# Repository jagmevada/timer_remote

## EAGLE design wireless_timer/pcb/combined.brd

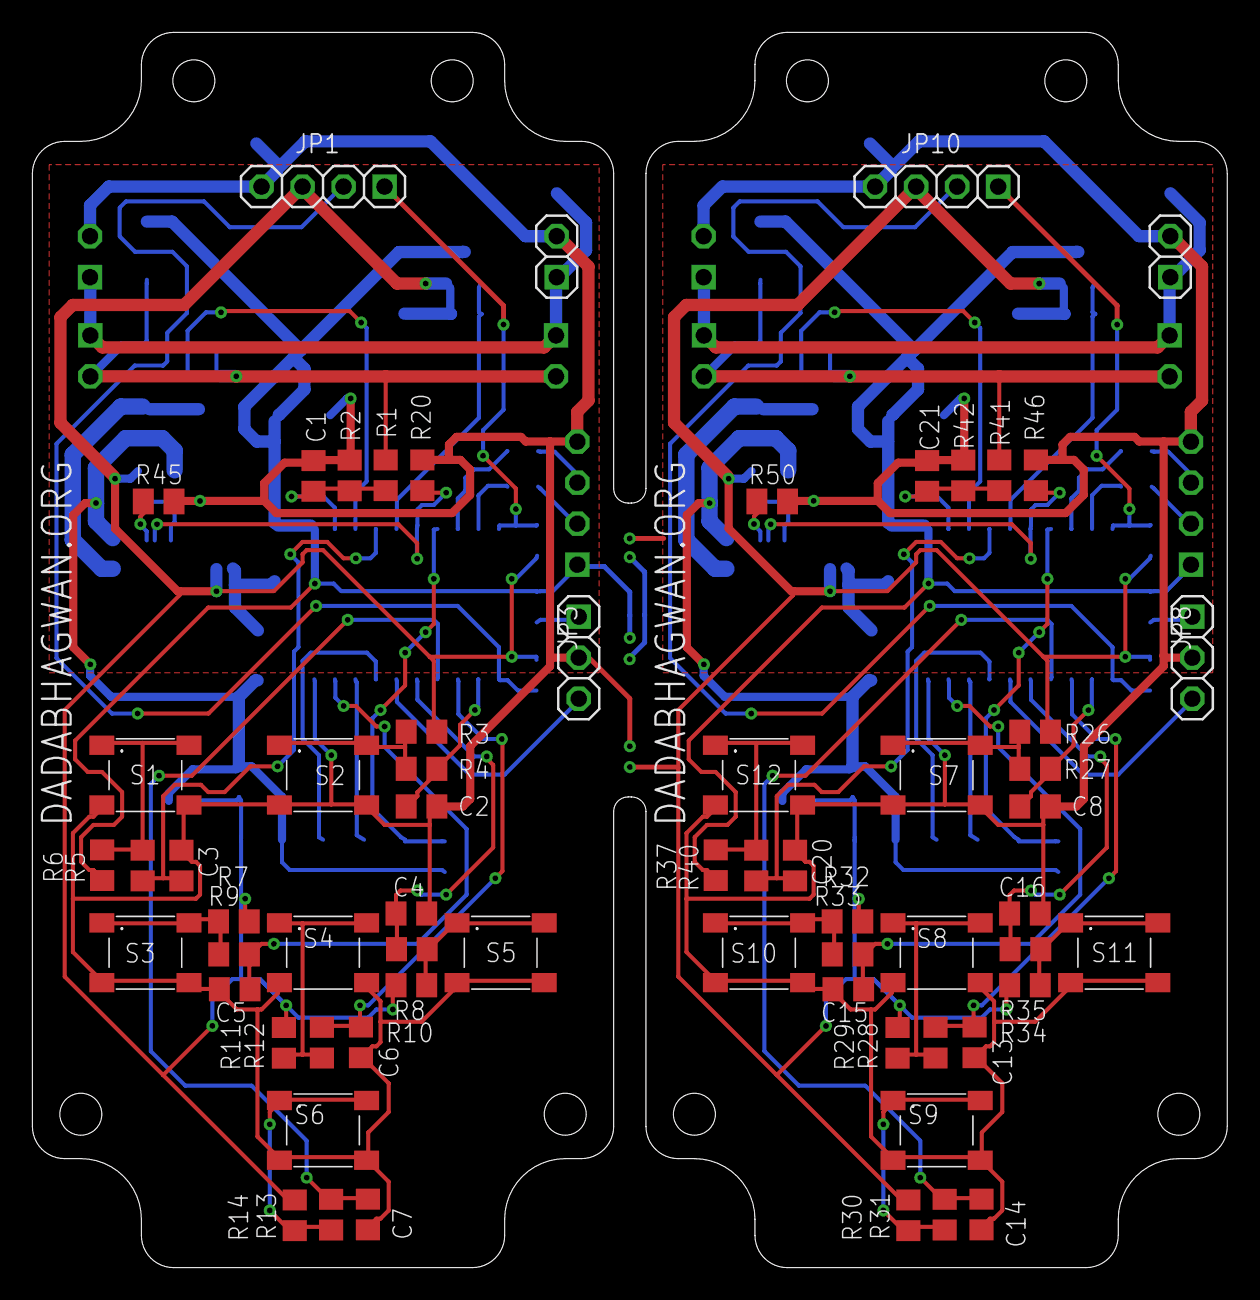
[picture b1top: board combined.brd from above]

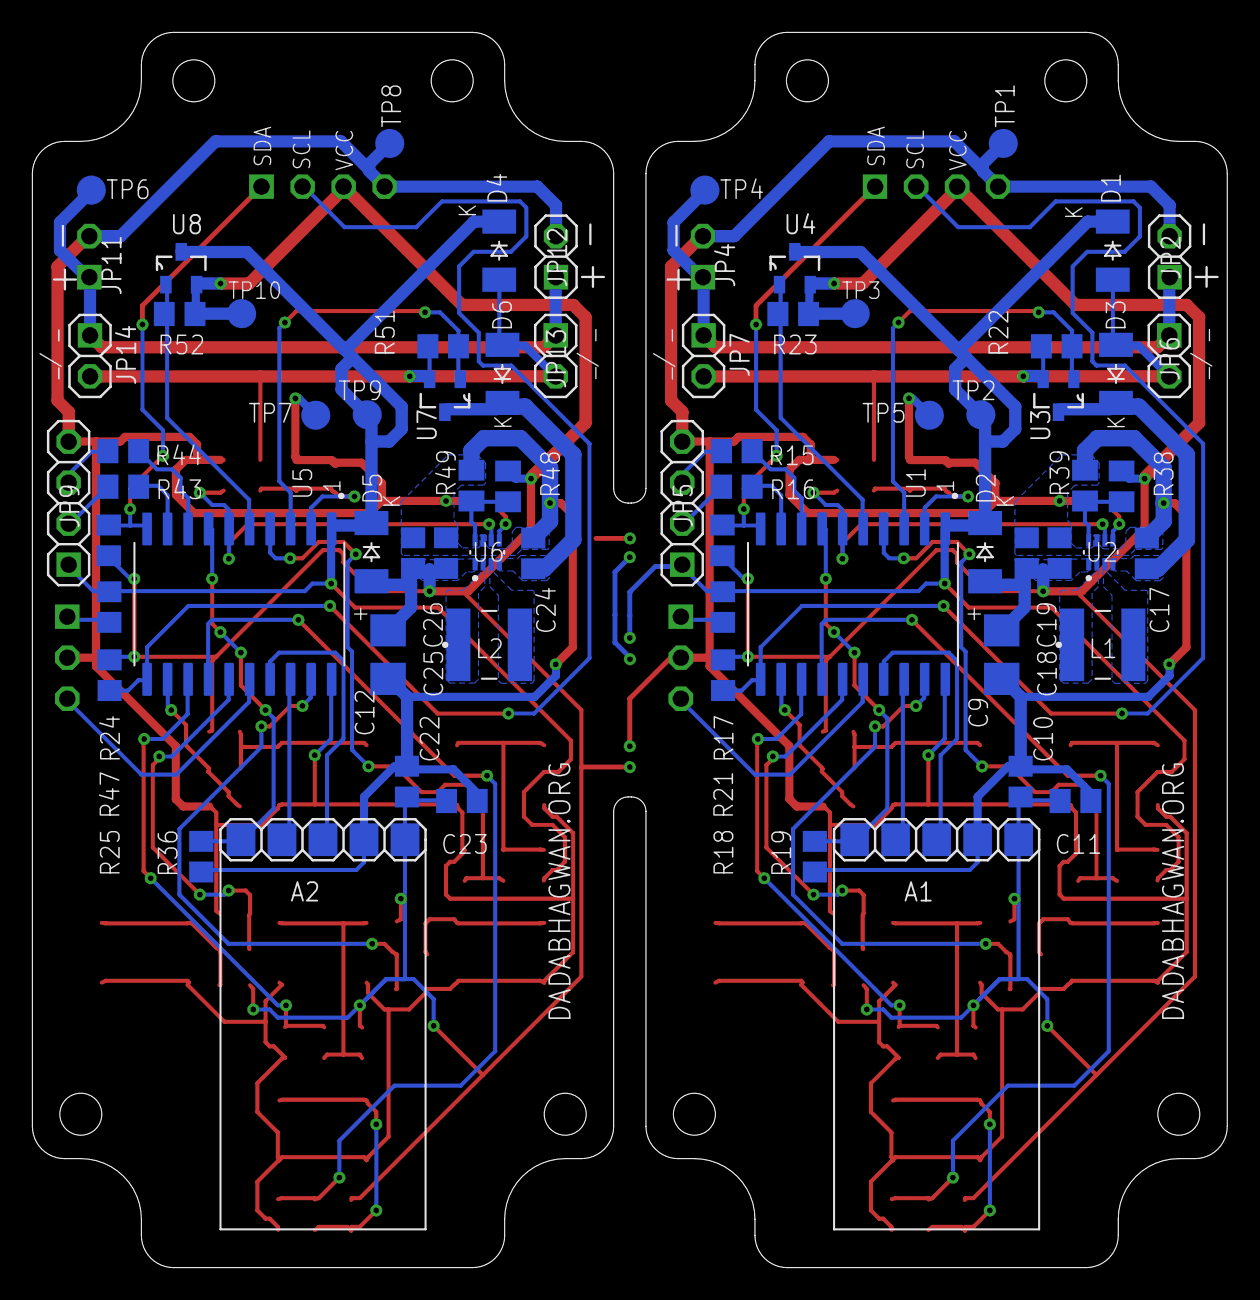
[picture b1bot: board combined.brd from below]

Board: 2 copper layers, 74.0 x 76.5 mm, 132 parts (68 on the bottom side), 74 nets.

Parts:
A1, A2: 1X05; 1X05X254
C1, C2, C3, C4, C5, C6, C7, C8, C13, C14, C15, C16, C20, C21: 100nF; C0805
C9, C12: 10uF; CT3528
C10, C11, C17, C18, C19, C22, C23, C24, C25, C26: 10uF; C0805
D1, D2, D3, D4, D5, D6: BAT; SOD-123_MINI-SMA
JP1, JP5, JP9, JP10: 1X04-S
JP2, JP4, JP6, JP7, JP11, JP12, JP13, JP14: 1X02-S
JP3, JP8: 1X03-S
L1, L2: 1uH; IND_74404043220A
R1, R2, R22, R23, R41, R42, R51, R52: 100K; R0805
R3, R4, R5, R6, R7, R8, R9, R10, R11, R12, R13, R14, R26, R27, R28, R29, R30, R31, R32, R33, R34, R35, R37, R40: 10K; R0805
R15, R16, R43, R44: 1K; R0805
R17, R18, R19, R20, R24, R25, R36, R46: 30K; R0805
R21, R47: 200E; R0805
R38, R48: 511K; M0805
R39, R49: 91K; M0805
R45, R50: 50K; M0805
S1, S2, S3, S4, S5, S6, S7, S8, S9, S10, S11, S12: SW; SW_55MM
TP1, TP5, TP7, TP8: GND; TP18R
TP2, TP9: VDD; TP18R
TP3, TP10: VCC; TP18R
TP4, TP6: VBAT; TP18R
U1, U5: 1; SOIC127P1032X265-20N
U2, U6: TPS; SOTFL50P160X60-8N
U3, U4, U7, U8: PMOS; SOT103P240X110-3N

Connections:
DC_SW: R22.1, U1.3, U3.1
DC_SW1: R51.1, U5.3, U7.1
GND: A1.2, C1.2, C2.2, C3.2, C4.2, C5.2, C6.2, C7.2, C9.-, C10.2, C11.2, C17.2, C18.2, C19.2, JP1.4, JP2.2, JP3.2, JP4.2, JP5.4, R2.2, R19.1, R20.1, R39.1, R45.1, S1.3, S1.4, S2.3, S2.4, S3.3, S3.4, S4.3, S4.4, S5.3, S5.4, S6.3, S6.4, TP1.TP, TP5.TP, U1.20, U2.7
GND1: A2.2, C8.2, C12.-, C13.2, C14.2, C15.2, C16.2, C20.2, C21.2, C22.2, C23.2, C24.2, C25.2, C26.2, JP8.2, JP9.4, JP10.4, JP11.2, JP12.2, R36.1, R42.2, R46.1, R49.1, R50.1, S7.3, S7.4, S8.3, S8.4, S9.3, S9.4, S10.3, S10.4, S11.3, S11.4, S12.3, S12.4, TP7.TP, TP8.TP, U5.20, U6.7
LX1: L1.2, U2.3
LX2: L1.1, U2.2
LX3: L2.2, U6.3
LX4: L2.1, U6.2
unnamed: R5.2, R6.1, S1.1, S1.2
unnamed: JP3.3, U1.16
unnamed: JP3.1, R21.2
unnamed: R26.1, R27.2, S7.1, S7.2
unnamed: R11.2, R12.1, S4.1, S4.2
unnamed: R28.1, R29.2, S8.1, S8.2
unnamed: R30.1, R31.2, S9.1, S9.2
unnamed: R13.2, R14.1, S6.1, S6.2
unnamed: R7.1, R9.2, S3.1, S3.2
unnamed: R8.2, R10.1, S5.1, S5.2
unnamed: R32.1, R33.2, S10.1, S10.2
unnamed: R3.1, R4.2, S2.1, S2.2
unnamed: R34.1, R35.2, S11.1, S11.2
unnamed: R37.1, R40.2, S12.1, S12.2
unnamed: JP8.3, U5.16
unnamed: JP8.1, R47.2
unnamed: R48.1, R49.2, U6.8
unnamed: R50.2, U6.5
unnamed: R38.1, R39.2, U2.8
unnamed: R45.2, U2.5
RXD0: R15.2, U1.8
RXD00: JP5.3, R15.1
RXD1: A1.4, U1.18
RXD02: R44.2, U5.8
RXD03: A2.4, U5.18
RXD04: JP9.3, R44.1
S1: C2.1, R4.1, U1.12
S2: C6.1, R11.1, U1.13
S3: C7.1, R13.1, U1.14
S4: C5.1, R9.1, U1.19
S5: C4.1, R8.1, U1.15
S6: C3.1, R5.1, U1.4
S7: C8.1, R27.1, U5.12
S8: C13.1, R29.1, U5.13
S9: C14.1, R31.1, U5.14
S10: C15.1, R33.1, U5.19
S11: C16.1, R35.1, U5.15
S12: C20.1, R40.1, U5.4
SCL: JP1.2, R18.2, U1.11
SCL1: JP10.2, R25.2, U5.11
SDA: JP1.1, R17.2, U1.10
SDA1: JP10.1, R24.2, U5.10
SET: A1.5, R19.2, U1.7
SET1: A2.5, R36.2, U5.7
SHDN: R20.2, U1.6, U2.6
SHDN1: R46.2, U5.6, U6.6
TXD0: R16.2, U1.9
TXD00: JP5.2, R16.1
TXD1: A1.3, U1.17
TXD02: R43.2, U5.9
TXD03: A2.3, U5.17
TXD04: JP9.2, R43.1
VADC: C1.1, R1.1, R2.1, U1.2
VADC1: C21.1, R41.1, R42.1, U5.2
VBAT: JP2.1, JP4.1, JP6.1, JP7.1, TP4.TP
VBAT1: JP11.1, JP12.1, JP13.1, JP14.1, TP6.TP
VBAT_O: D1.A, D3.A, JP6.2, JP7.2, R1.2, R22.2, U3.2
VBAT_O1: D4.A, D6.A, JP13.2, JP14.2, R41.2, R51.2, U7.2
VCC: A1.1, C9.+, C10.1, C11.1, C18.1, C19.1, D2.A, JP1.3, R3.2, R7.2, R10.2, R12.2, R14.2, R17.1, R18.1, R23.1, R38.2, TP3.TP, U2.1, U4.2
VCC1: A2.1, C12.+, C22.1, C23.1, C25.1, C26.1, D5.A, JP10.3, R24.1, R25.1, R26.2, R28.2, R30.2, R32.2, R34.2, R48.2, R52.1, TP10.TP, U6.1, U8.2
VCC_SW: R23.2, U1.5, U4.1
VCC_SW1: R52.2, U5.5, U8.1
VDD: D1.C, D2.C, JP5.1, R6.2, R21.1, TP2.TP, U1.1, U4.3
VDD1: D4.C, D5.C, JP9.1, R37.2, R47.1, TP9.TP, U5.1, U8.3
VIN: C17.1, D3.C, U2.4, U3.3
VIN1: C24.1, D6.C, U6.4, U7.3

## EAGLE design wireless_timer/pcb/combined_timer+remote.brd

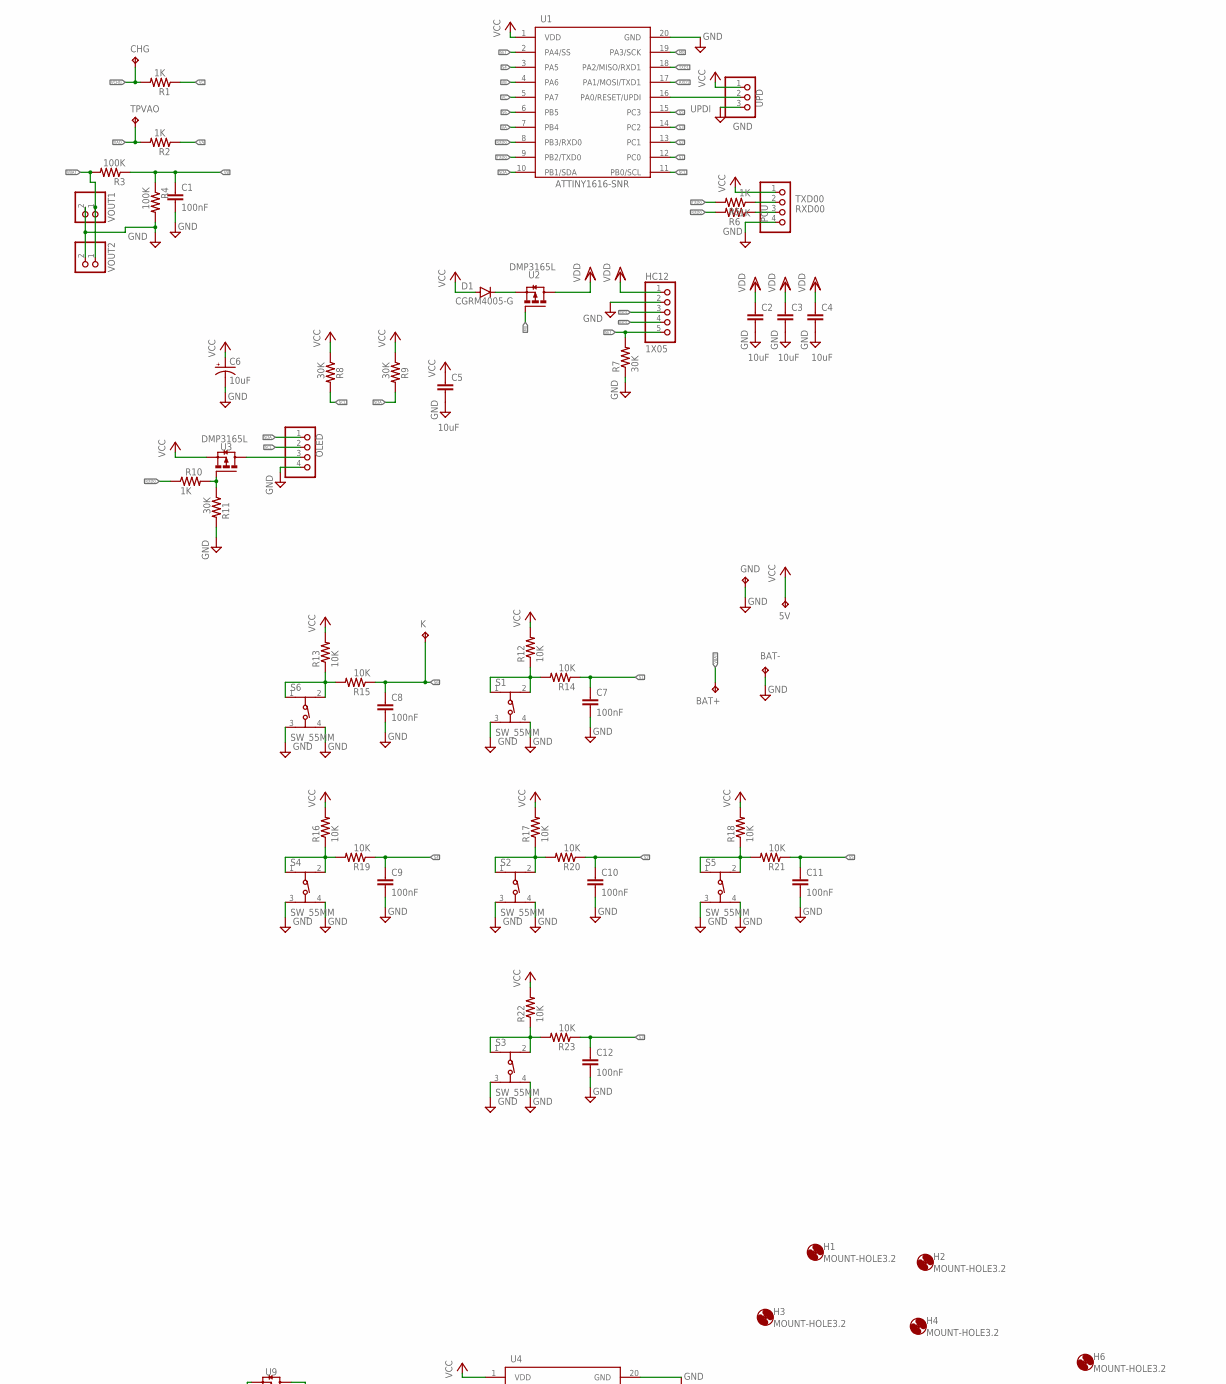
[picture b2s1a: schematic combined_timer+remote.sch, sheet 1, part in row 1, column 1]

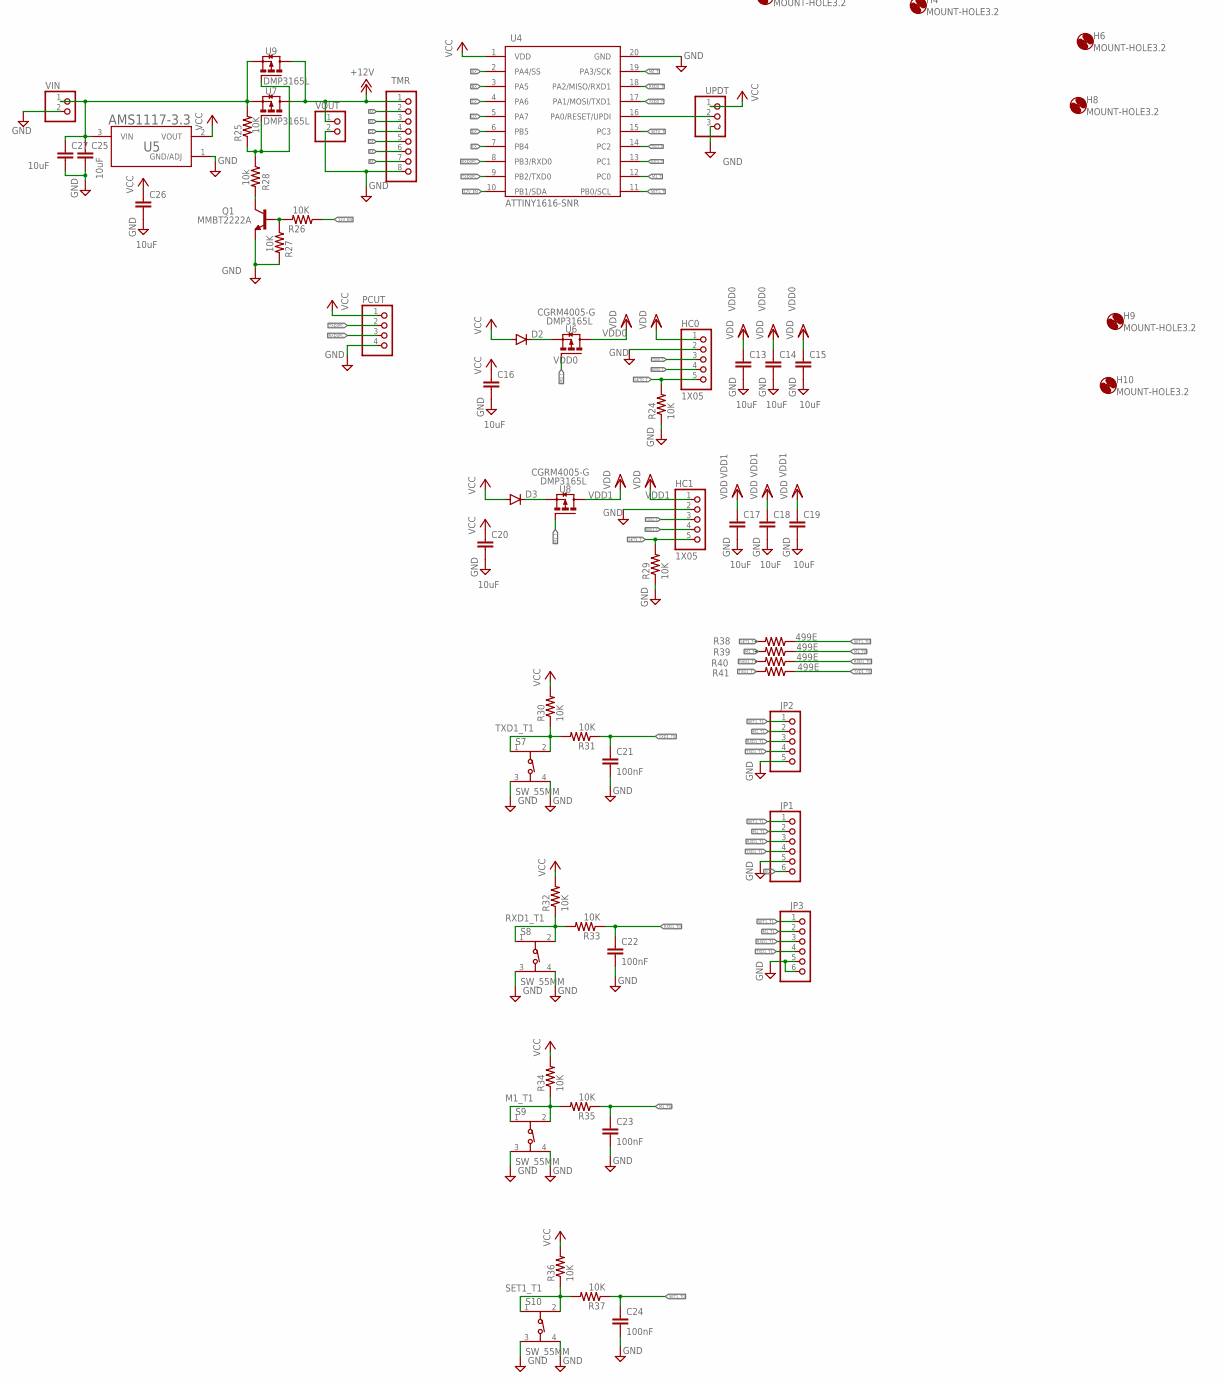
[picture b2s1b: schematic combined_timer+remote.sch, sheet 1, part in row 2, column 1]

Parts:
5V: TPTP18R; TP18R
BAT+: TPTP18R; TP18R
BAT-: TPTP18R; TP18R
C1, C7, C8, C9, C10, C11, C12, C21, C22, C23, C24: 100nF; C0603K
C2, C3, C4, C5, C13, C14, C15, C16, C17, C18, C19, C20, C25, C26, C27: 10uF; C0805
C6: 10uF; CT3528
CHG: TPTP18R; TP18R
D1, D2, D3: CGRM4005-G; SOD-123_MINI-SMA
GND: TPTP18R; TP18R
H1, H2, H3, H4, H6, H8, H9, H10: MOUNT-HOLE3.2; 3,2
HC0, HC1, HC12: 1X05; 1X05X254
JP1, JP3: PINHD-1X06_2.54-S; 1X06-S
JP2: PINHD-1X5; 1X05
K: TPTP18R; TP18R
OLED: PINHD-1X04_2.54-S; 1X04-S
PCU: PINHD-1X04_2.54-S; 1X04-S
PCUT: PINHD-1X04_2.54-S; 1X04-S
Q1: MMBT2222A; SOT23
R1, R2, R10: 1K; R0603
R3, R4: 100K; R0603
R5, R6: 1K; R0805
R7, R8, R9, R11: 30K; R0603
R12, R13, R14, R15, R16, R17, R18, R19, R20, R21, R22, R23, R24, R25, R26, R27, R29, R30, R31, R32, R33, R34, R35, R36, R37: 10K; R0603
R28: 10k; R0603
R38, R39, R40, R41: 499E; R0603
S1, S2, S3, S4, S5, S6, S7, S8, S9, S10: SW_55MM
TMR: PINHD-1X08_2.54-S; 1X08-S
TPVAO: TPTP18R; TP18R
U1, U4: ATTINY1616-SNR; SOIC127P1032X265-20N
U2, U3, U6, U7, U8, U9: DMP3165L; SOT103P240X110-3N
U5: AMS1117-3.3; SOT229P700X180-4N
UPD: PINHD-1X03_2.54-S; 1X03-S
UPDT: PINHD-1X03_2.54-S; 1X03-S
VIN: PINHD-1X2; 1X02
VOUT: PINHD-1X2; 1X02
VOUT1, VOUT2: PINHD-1X02_2.54-S; 1X02-S

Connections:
12VIN: C25.1, C27.1, R25.2, U5.3 (VIN), U7.2 (S), U9.2 (S), VIN.1
12V_EN: R26.1, U4.10 (PB1/SDA)
+12V: TMR.1, U7.3 (D), U9.3 (D), VOUT.1
AX: TMR.2, U4.2 (PA4/SS)
BX: TMR.3, U4.3 (PA5)
CX: TMR.4, U4.4 (PA6)
DX: TMR.5, U4.5 (PA7)
EX: TMR.6, U4.6 (PB5)
FX: TMR.7, U4.7 (PB4)
GND: BAT-.TP, C1.2, C2.2, C3.2, C4.2, C5.2, C6.-, C7.2, C8.2, C9.2, C10.2, C11.2, C12.2, C13.2, C14.2, C15.2, C16.2, C17.2, C18.2, C19.2, C20.2, C21.2, C22.2, C23.2, C24.2, C25.2, C26.2, C27.2, GND.TP, HC0.2, HC1.2, HC12.2, JP1.5, JP2.5, JP3.5, JP3.6, OLED.4, PCU.4, PCUT.4, Q1.2 (E), R4.2, R7.1, R11.2, R24.1, R27.2, R29.1, S1.3, S1.4, S2.3, S2.4, S3.3, S3.4, S4.3, S4.4, S5.3, S5.4, S6.3, S6.4, S7.3, S7.4, S8.3, S8.4, S9.3, S9.4, S10.3, S10.4, TMR.8, U1.20 (GND), U4.20 (GND), U5.1 (GND/ADJ), UPD.3, UPDT.3, VIN.2, VOUT.2, VOUT1.2, VOUT2.2
M0: U1.19 (PA3/SCK), U2.1 (G)
M0_T: U4.19 (PA3/SCK), U6.1 (G)
M1_T: R39.2, U4.12 (PC0), U8.1 (G)
M1_T0: C23.1, R35.1, R39.1
M1_T1: JP1.2, JP2.2, JP3.2, R34.1, R35.2, S9.1, S9.2
unnamed: R13.1, R15.2, S6.1, S6.2
unnamed: D1.C, U2.2 (S)
unnamed: OLED.3, U3.3 (D)
unnamed: R10.2, R11.1, U3.1 (G)
unnamed: R17.1, R20.2, S2.1, S2.2
unnamed: D2.C, U6.2 (S)
unnamed: R22.1, R23.2, S3.1, S3.2
unnamed: R16.1, R19.2, S4.1, S4.2
unnamed: R18.1, R21.2, S5.1, S5.2
unnamed: Q1.1 (B), R26.2, R27.1
unnamed: R12.1, R14.2, S1.1, S1.2
unnamed: Q1.3 (C), R28.2
unnamed: D3.C, U8.2 (S)
unnamed: R25.1, R28.1, U7.1 (G), U9.1 (G)
unnamed: U4.16 (PA0/RESET/UPDI), UPDT.2
RXD0: R6.2, R10.1, U1.8 (PB3/RXD0)
RXD00: PCU.3, R6.1
RXD0PC: PCUT.3, U4.8 (PB3/RXD0)
RXD0_T: HC0.4, U4.18 (PA2/MISO/RXD1)
RXD1: HC12.4, U1.17 (PA1/MOSI/TXD1)
RXD1_T: HC1.4, R40.2, U4.13 (PC1)
RXD1_T0: C22.1, R33.1, R40.1
RXD1_T1: JP1.3, JP2.3, JP3.3, R32.1, R33.2, S8.1, S8.2
S1: C7.1, R14.1, U1.12 (PC0)
S2: C10.1, R20.1, U1.13 (PC1)
S3: C12.1, R23.1, U1.14 (PC2)
S4: C9.1, R19.1, U1.3 (PA5)
S5: C11.1, R21.1, U1.15 (PC3)
S6: C8.1, K.TP, R15.1, U1.6 (PB5)
SCL: JP1.6, OLED.2, R8.2, U1.11 (PB0/SCL)
SDA: OLED.1, R9.2, U1.10 (PB1/SDA)
SET: HC12.5, R7.2, U1.2 (PA4/SS)
SET0_T: HC0.5, R24.2, U4.15 (PC3)
SET1_T: HC1.5, R29.2, R38.2, U4.11 (PB0/SCL)
SET1_T0: C24.1, R37.1, R38.1
SET1_T1: JP1.1, JP2.1, JP3.1, R36.1, R37.2, S10.1, S10.2
TXD0: R5.2, U1.9 (PB2/TXD0)
TXD00: PCU.2, R5.1
TXD0PC: PCUT.2, U4.9 (PB2/TXD0)
TXD0_T: HC0.3, U4.17 (PA1/MOSI/TXD1)
TXD1: HC12.3, U1.18 (PA2/MISO/RXD1)
TXD1_T: HC1.3, R41.2, U4.14 (PC2)
TXD1_T0: C21.1, R31.1, R41.1
TXD1_T1: JP1.4, JP2.4, JP3.4, R30.1, R31.2, S7.1, S7.2
UPDI: U1.16 (PA0/RESET/UPDI), UPD.2
VA: R2.1, U1.7 (PB4)
VAO: R2.2, TPVAO.TP
VB: C1.1, R3.1, R4.1, U1.4 (PA6)
VBAT: BAT+.TP, R3.2, VOUT1.1, VOUT2.1
VC: R1.1, U1.5 (PA7)
VCC: 5V.TP, C5.1, C6.+, C16.1, C20.1, C26.1, D1.A, D2.A, D3.A, PCU.1, PCUT.1, R8.1, R9.1, R12.2, R13.2, R16.2, R17.2, R18.2, R22.2, R30.2, R32.2, R34.2, R36.2, U1.1 (VDD), U3.2 (S), U4.1 (VDD), U5.2 (VOUT), UPD.1, UPDT.1
VCHG: CHG.TP, R1.2
VDD: C2.1, C3.1, C4.1, HC12.1, U2.3 (D)
VDD0: C13.1, C14.1, C15.1, HC0.1, U6.3 (D)
VDD1: C17.1, C18.1, C19.1, HC1.1, U8.3 (D)

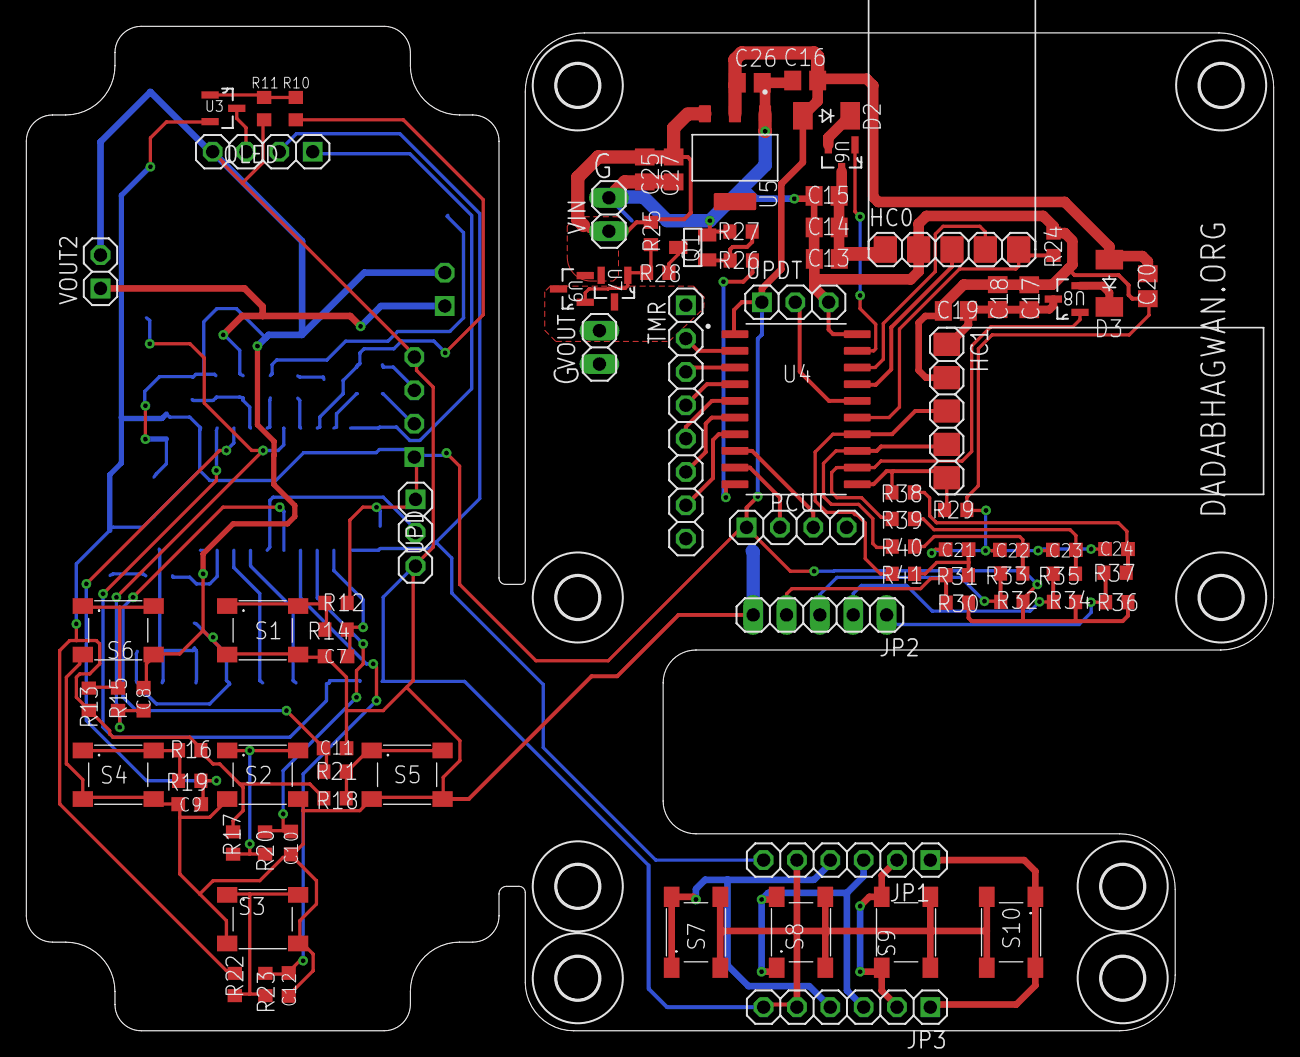
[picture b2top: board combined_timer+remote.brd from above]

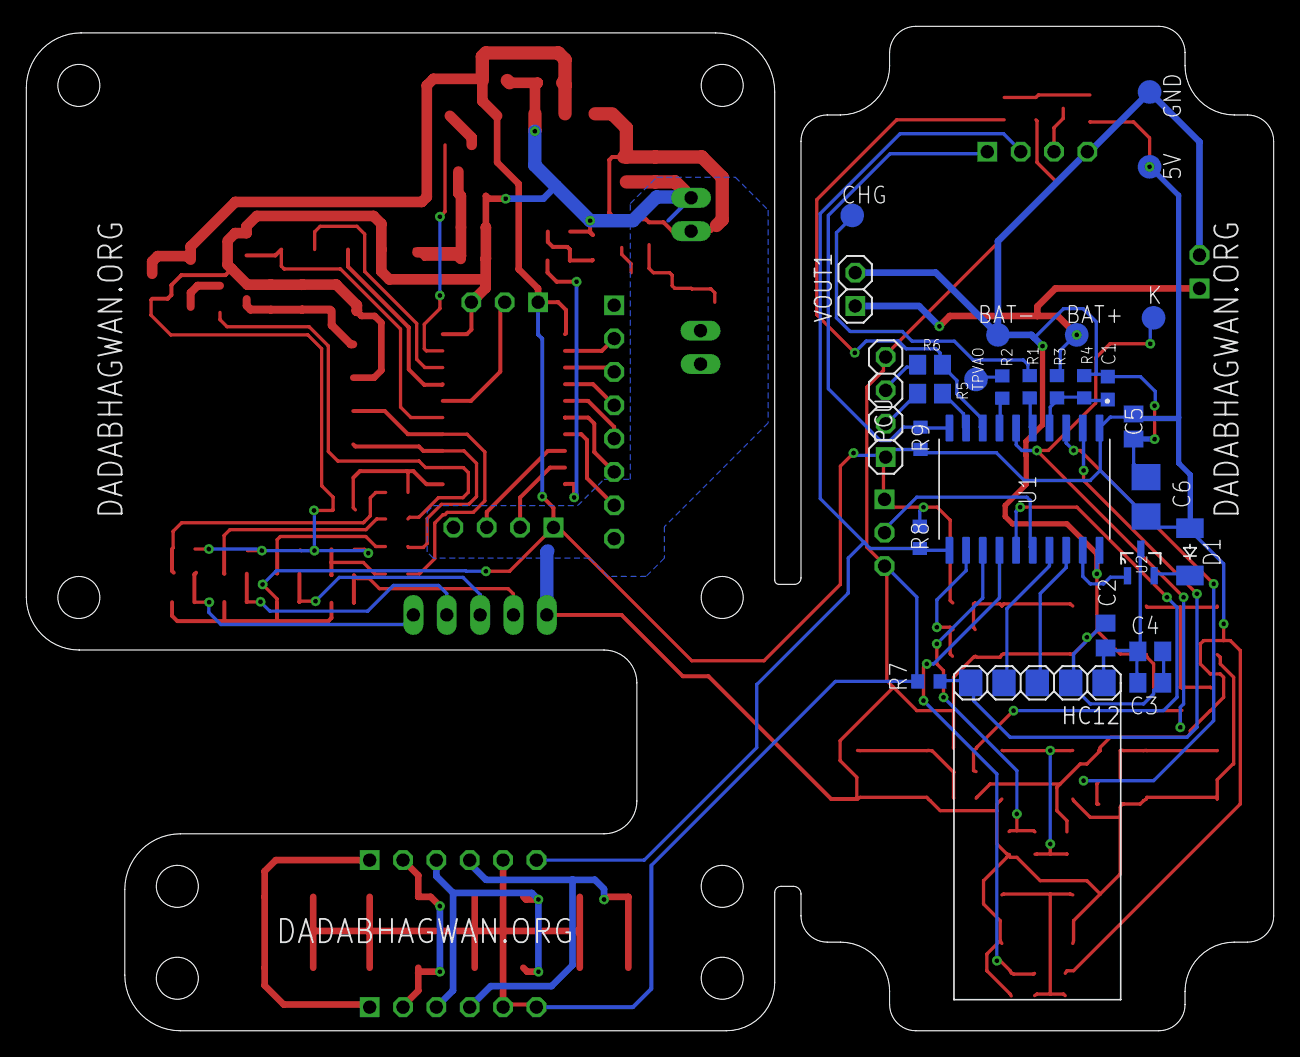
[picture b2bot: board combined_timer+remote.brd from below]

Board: 2 copper layers, 95.0 x 76.5 mm, 122 parts (28 on the bottom side), 70 nets.

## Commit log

2024-08-11 first commit, original timer pcb layout
2024-08-13 layout cleaned
2024-08-13 dcdc added
2024-08-14 ready for dcdc insertion
2024-08-14 layout completed
2024-08-14 panel made, outline pending
2024-08-14 panel completed, outline added
2024-08-14 gerber generated, cam file modified, ready for fab
2024-09-03 cad file added
